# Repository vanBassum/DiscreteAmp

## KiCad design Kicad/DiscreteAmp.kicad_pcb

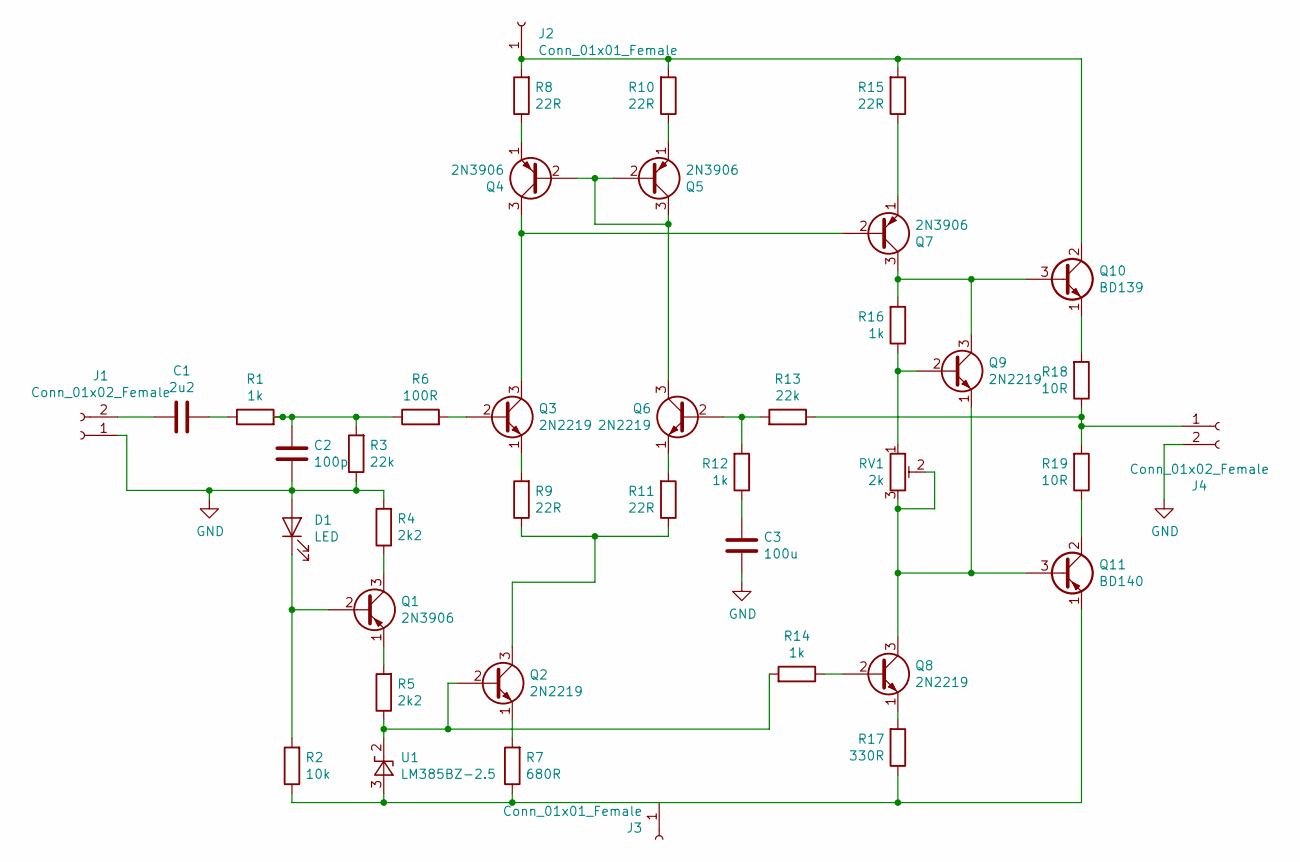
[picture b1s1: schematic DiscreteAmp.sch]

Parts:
C1: 2u2; CP_Radial_D5.0mm_P2.50mm
C2: 100p; C_Disc_D3.8mm_W2.6mm_P2.50mm
C3: 100u; CP_Radial_D8.0mm_P3.50mm
D1: LED; LED_D3.0mm
J1, J4: Conn_01x02_Female; SolderWirePad_1x02_P7.62mm_Drill2.5mm
J2, J3: Conn_01x01_Female; SolderWirePad_1x01_Drill2.5mm
Q1, Q4, Q5, Q7: 2N3906; TO-92S_Wide
Q2, Q3, Q6, Q8, Q9: 2N2219; TO-92S_Wide
Q10: BD139; TO-126-3_Vertical
Q11: BD140; TO-126-3_Vertical
R1, R12, R14, R16: 1k; R_Axial_DIN0207_L6.3mm_D2.5mm_P7.62mm_Horizontal
R2: 10k; R_Axial_DIN0207_L6.3mm_D2.5mm_P7.62mm_Horizontal
R3, R13: 22k; R_Axial_DIN0207_L6.3mm_D2.5mm_P7.62mm_Horizontal
R4, R5: 2k2; R_Axial_DIN0207_L6.3mm_D2.5mm_P7.62mm_Horizontal
R6: 100R; R_Axial_DIN0207_L6.3mm_D2.5mm_P7.62mm_Horizontal
R7: 680R; R_Axial_DIN0207_L6.3mm_D2.5mm_P7.62mm_Horizontal
R8, R9, R10, R11, R15: 22R; R_Axial_DIN0207_L6.3mm_D2.5mm_P7.62mm_Horizontal
R17: 330R; R_Axial_DIN0207_L6.3mm_D2.5mm_P7.62mm_Horizontal
R18, R19: 10R; R_Axial_DIN0614_L14.3mm_D5.7mm_P20.32mm_Horizontal
RV1: 2k; PinSocket_1x03_P2.54mm_Vertical
U1: LM385BZ-2.5; TO-92S_Wide

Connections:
GND: C2.2, C3.2, D1.2 (A), J1.1, J4.2, R3.1, R4.2
unnamed: C1.1, J1.2
unnamed: C1.2, R1.1
unnamed: C2.1, R1.2, R3.2, R6.1
unnamed: C3.1, R12.1
unnamed: D1.1 (K), Q1.2 (B), R2.2
unnamed: J2.1, Q10.2 (C), R8.2, R10.2, R15.2
unnamed: J4.1, R13.1, R18.1, R19.2
unnamed: Q1.1 (E), R5.2
unnamed: Q1.3 (C), R4.1
unnamed: Q2.1 (E), R7.2
unnamed: Q2.2 (B), R5.1, R14.2, U1.2 (K)
unnamed: Q2.3 (C), R9.1, R11.1
unnamed: Q3.1 (E), R9.2
unnamed: Q3.2 (B), R6.2
unnamed: Q3.3 (C), Q4.3 (C), Q7.2 (B)
unnamed: Q4.1 (E), R8.1
unnamed: Q4.2 (B), Q5.2 (B), Q5.3 (C), Q6.3 (C)
unnamed: Q5.1 (E), R10.1
unnamed: Q6.1 (E), R11.2
unnamed: Q6.2 (B), R12.2, R13.2
unnamed: Q7.1 (E), R15.1
unnamed: Q8.1 (E), R17.2
unnamed: Q8.2 (B), R14.1
unnamed: Q9.2 (B), R16.1, RV1.1
unnamed: Q10.1 (E), R18.2
unnamed: Q7.3 (C), Q9.3 (C), Q10.3 (B), R16.2
unnamed: Q11.2 (C), R19.1
unnamed: Q8.3 (C), Q9.1 (E), Q11.3 (B), RV1.2, RV1.3

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
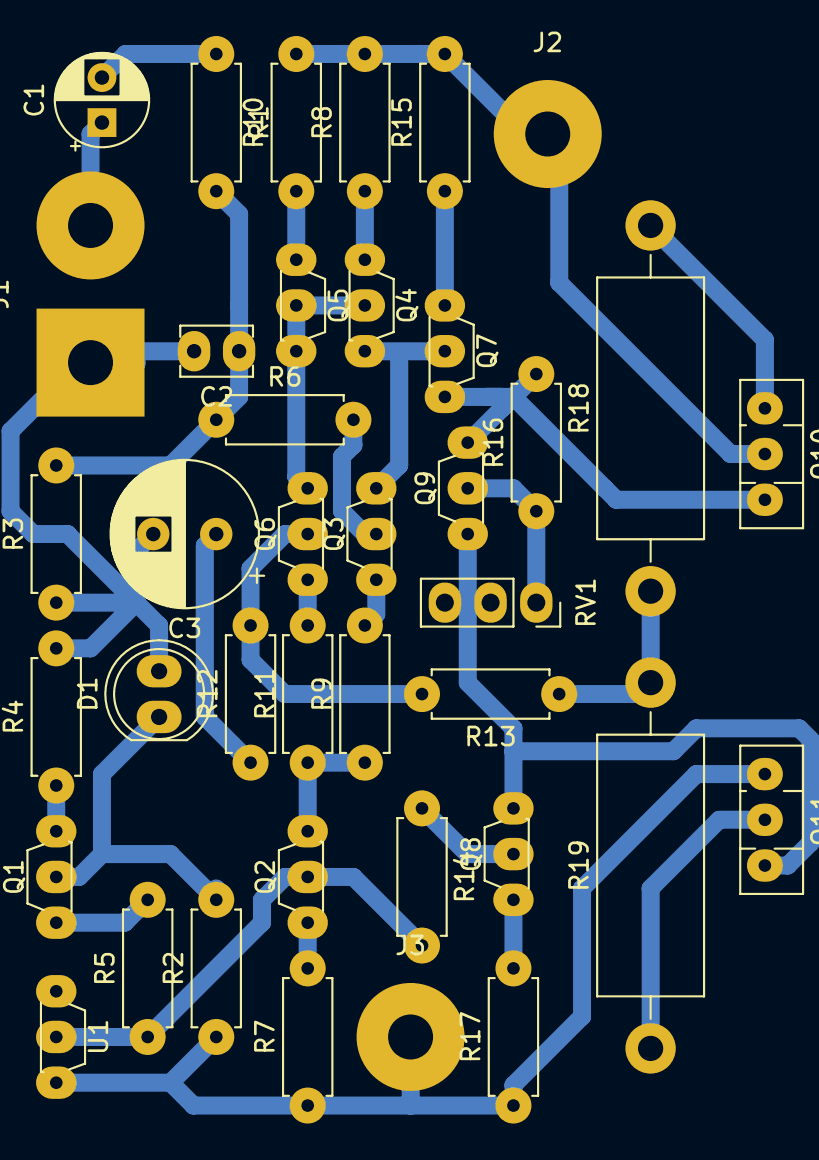
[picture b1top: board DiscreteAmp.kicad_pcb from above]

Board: 2 copper layers, 39 parts (0 on the bottom side), 30 nets.

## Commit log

2020-04-30 First design
2020-05-03 Fixed some 'bugs'
